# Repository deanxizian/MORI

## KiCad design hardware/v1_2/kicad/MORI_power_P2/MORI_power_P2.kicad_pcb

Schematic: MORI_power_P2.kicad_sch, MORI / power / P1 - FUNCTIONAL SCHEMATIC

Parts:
C1, C20, C40: 100n; C_0603_1608Metric
C2: 1u 25V; C_0603_1608Metric
C10: Panasonic EEU-FR1C102 1000uF 16V; CP_Radial_D10.0mm_P5.00mm__P2_C10
C21, C41: 10n; C_0603_1608Metric
C30: Panasonic EEU-FR1C102 1000uF 16V; CP_Radial_D10.0mm_P5.00mm
D1, D20, D40: BZT52H-C10,115; D_SOD-123F
D10, D30: B540C-13-F; D_SMC
H1, H2, H3, H4: M2 clearance; MountingHole_2.2mm_M2
J1: PACK AFTER 6.3A FUSE / MASTER; AMASS_XT30UPB-M_1x02_P5.0mm_Vertical
J2: WHEEL BUCK VIN; AMASS_XT30UPB-M_1x02_P5.0mm_Vertical
J3: WHEEL BUCK 9V RETURN; AMASS_XT30UPB-M_1x02_P5.0mm_Vertical
J4: HEAD BUCK VIN; AMASS_XT30UPB-M_1x02_P5.0mm_Vertical__P2_J4
J5: HEAD BUCK 6V RETURN; AMASS_XT30UPB-M_1x02_P5.0mm_Vertical__P2_J5
J6: LOGIC BUCKS VIN / FUSED HARNESS; AMASS_XT30UPB-M_1x02_P5.0mm_Vertical
J7: S288 L; JST_XH_B3B-XH-A_1x03_P2.50mm_Vertical__P2_J7
J8: S288 R; JST_XH_B3B-XH-A_1x03_P2.50mm_Vertical__P2_J8
J9: SCS0009 CHAIN; JST_XH_B3B-XH-A_1x03_P2.50mm_Vertical
J10: MOTION CONTROL; JST_GH_BM08B-GHS-TBT_1x08-1MP_P1.25mm_Vertical__P2_J10
J11: WHEEL DUMP 5R6 EXTERNAL; AMASS_XT30UPB-M_1x02_P5.0mm_Vertical
J12: HEAD DUMP 10R EXTERNAL; AMASS_XT30UPB-M_1x02_P5.0mm_Vertical__P2_J12
J13: S288 DATA; JST_GH_BM02B-GHS-TBT_1x02-1MP_P1.25mm_Vertical__P2_J13
J14: HEAD DATA; JST_GH_BM03B-GHS-TBT_1x03-1MP_P1.25mm_Vertical
J15: CHARGE INTERLOCK; JST_GH_BM02B-GHS-TBT_1x02-1MP_P1.25mm_Vertical
J16: CHARGER RAW VBUS SENSE; JST_GH_BM02B-GHS-TBT_1x02-1MP_P1.25mm_Vertical__P2_J16
Q1, Q10, Q30: AO4407A; SOIC-8_3.9x4.9mm_P1.27mm
Q11, Q20, Q31, Q40: AO3400A; SOT-23
Q50: MMBT3904LT1G; SOT-23
R1, R10, R30, R54: 10k; R_0603_1608Metric
R2: WSL2512R0100FEA 10mR 1% 1W; R_2512_6332Metric
R3, R4: 0; R_0603_1608Metric
R11, R31: 100; R_0603_1608Metric
R20, R24, R40, R44: 2.2k; R_0603_1608Metric
R21: 33.2k 0.1%; R_0603_1608Metric
R22, R26, R42, R46: 10k 0.1%; R_0603_1608Metric
R23, R43: 1M 0.1%; R_0603_1608Metric
R25: 37.4k 0.1%; R_0603_1608Metric
R41: 16.5k 0.1%; R_0603_1608Metric
R45: 18.7k 0.1%; R_0603_1608Metric
R50, R52: 100k 0.1%; R_0603_1608Metric
R51, R53: 27k 0.1%; R_0603_1608Metric
R55: 47k; R_0603_1608Metric
R56: 100k; R_0603_1608Metric
U1: INA180A1IDBVR; SOT-23-5
U20, U40: LM393BDR; SOIC-8_3.9x4.9mm_P1.27mm
U21, U41: TL431BIDBZR; SOT-23

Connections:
/+3V3: C1.1, J10.1, U1.5 (VS)
/ARM_Q: J10.2, Q11.1, Q31.1, R54.1
/BAT_ADC: J10.5, R50.2, R51.1
/BAT_IN: J1.2 (PLUS), Q1.5, Q1.6, Q1.7, Q1.8
/BAT_MON: C2.1, J2.2 (PLUS), J4.2 (PLUS), J6.2 (PLUS), R2.2, R4.1, R50.1
/BAT_REV: D1.1, Q1.1 (SOURCE PROTECTED OUTPUT), Q1.2, Q1.3, R2.1, R3.1
/CHG_BASE: Q50.1 (B), R55.2, R56.1
/CHG_N: J10.4, J15.1, Q50.3 (C)
/CURRENT_ADC: J10.7, U1.1 (OUT)
/FAULT_N: J10.3, U20.7 (OUT2), U40.7 (OUT2)
/GND: C1.2, C2.2, C10.2, C20.2, C21.2, C30.2, C40.2, C41.2, D20.2, D40.2, J1.1 (MINUS), J2.1 (MINUS), J3.1 (MINUS), J4.1 (MINUS), J5.1 (MINUS), J6.1 (MINUS), J7.1 (GND), J8.1 (GND), J9.1 (GND), J10.8, J13.2, J14.2, J15.2, J16.2, Q11.2, Q20.2, Q31.2, Q40.2, Q50.2 (E), R1.2, R22.2, R26.2, R42.2, R46.2, R51.2, R53.2, R54.2, R56.2, U1.2 (GND), U20.4 (GND), U21.3 (A), U40.4 (GND), U41.3 (A)
/H6_IN: D30.2, J5.2 (PLUS)
/H_BRAKE_GATE: D40.1, Q40.1, R43.1, R44.2, U40.1 (OUT1)
/H_BUS: J9.3 (BUS), J14.1
/H_DUMP_D: J12.1 (MINUS), Q40.3
/H_GATE: Q30.4, R30.1, R31.1
/H_GATE_LOW: Q31.3, R31.2
/H_OVSENSE: C41.1, R45.2, R46.1, U40.6 (IN2-)
/H_PRE: D30.1, Q30.1, Q30.2, Q30.3, R30.2
/H_REF: R40.2, U40.2 (IN1-), U40.5 (IN2+), U41.1 (K), U41.2 (REF)
/H_SENSE: R41.2, R42.1, R43.2, U40.3 (IN1+)
/H_VM: C30.1, C40.1, J9.2 (V+), J12.2 (PLUS), Q30.5 (DRAIN SWITCHED OUTPUT), Q30.6, Q30.7, Q30.8, R40.1, R41.1, R44.1, R45.1, U40.8 (VCC)
/KELVIN_N: R4.2, U1.4 (IN-)
/KELVIN_P: R3.2, U1.3 (IN+)
/REV_GATE: D1.2, Q1.4, R1.1
/VBUS_CHARGE: J16.1, R55.1
/W9_IN: D10.2, J3.2 (PLUS)
/WHEEL_ADC: J10.6, R52.2, R53.1
/W_BRAKE_GATE: D20.1, Q20.1, R23.1, R24.2, U20.1 (OUT1)
/W_BUS: J7.3 (BUS), J8.3 (BUS), J13.1
/W_DUMP_D: J11.1 (MINUS), Q20.3
/W_GATE: Q10.4, R10.1, R11.1
/W_GATE_LOW: Q11.3, R11.2
/W_OVSENSE: C21.1, R25.2, R26.1, U20.6 (IN2-)
/W_PRE: D10.1, Q10.1, Q10.2, Q10.3, R10.2
/W_REF: R20.2, U20.2 (IN1-), U20.5 (IN2+), U21.1 (K), U21.2 (REF)
/W_SENSE: R21.2, R22.1, R23.2, U20.3 (IN1+)
/W_VM: C10.1, C20.1, J7.2 (V+), J8.2 (V+), J11.2 (PLUS), Q10.5 (DRAIN SWITCHED OUTPUT), Q10.6, Q10.7, Q10.8, R20.1, R21.1, R24.1, R25.1, R52.1, U20.8 (VCC)

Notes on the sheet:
MORI / POWER CONDITIONER / S2
Power flows left to right. Supplies above, returns below. PROTOTYPE / UNVALIDATED.
01 Pack input / reverse protection / shunt
External pack, fuse and master switch precede J1. No charger on this PCB.
10mR / 1% / 1W
02 Kelvin current sense
Sense from the shunt pads. Discharge-only nominal transfer: 0.2 V/A.
03 Wheel 9 V conditioning
External buck return. Inrush, brake energy and thermal performance: NOT_TESTED.
1000u / 16V
04 Head 6 V conditioning
05 External converter input distribution
J2 -> wheel buck; J4 -> head buck; J6 -> two independent 5 V converters.
06 Wheel rail / brake and overvoltage
Two comparators share one LM393B. External dump resistor needs pulse qualification.
LM393B / brake + fault
5R6 / 5W external
07 Head rail / brake and overvoltage
10R / 5W external
08 Voltage monitor / motion connector
Divider ratio 27 / 127. Current_ADC comes from block 02.
09 Charge insertion / VBUS sense
Sense and interlock only; no CC / PD / CC-CV charger implementation.
10 Supply boundaries / board mounting
80 x 45 mm PCB; populated assembly and thermal performance are not qualified.
Supply boundary

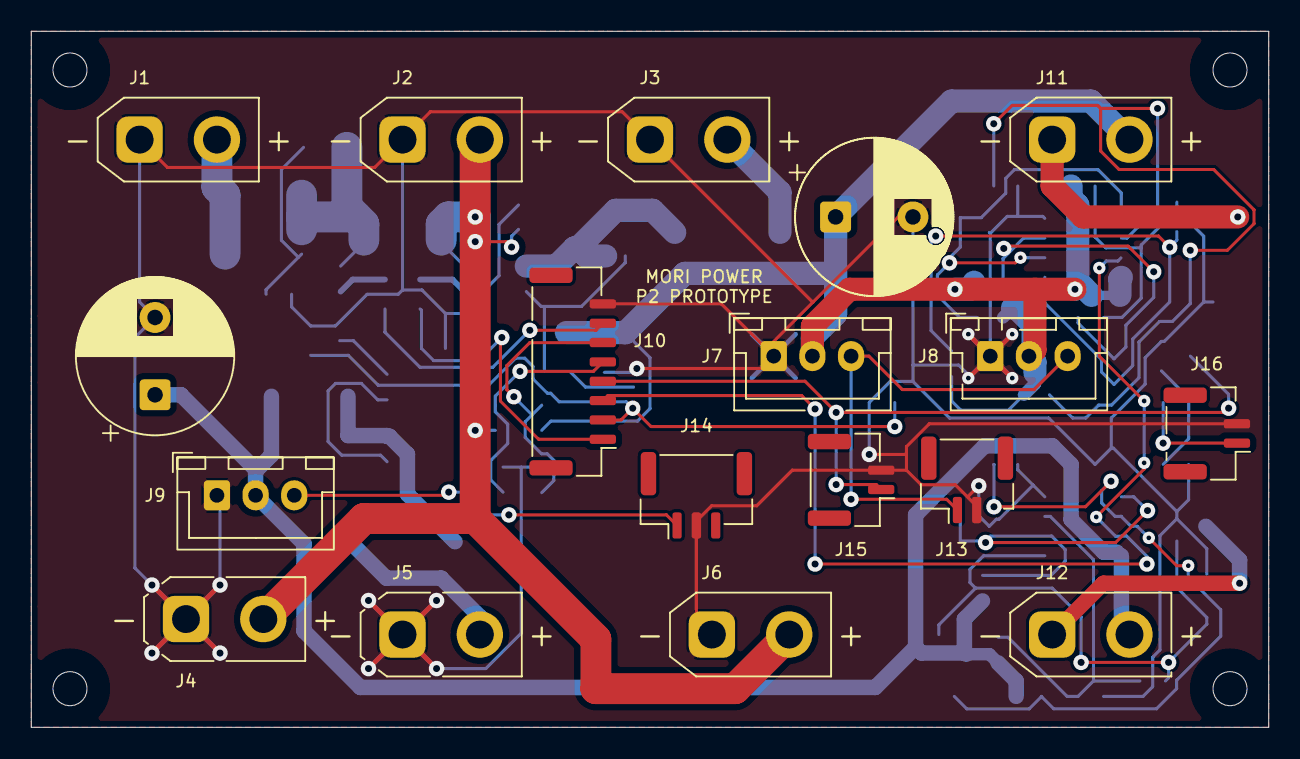
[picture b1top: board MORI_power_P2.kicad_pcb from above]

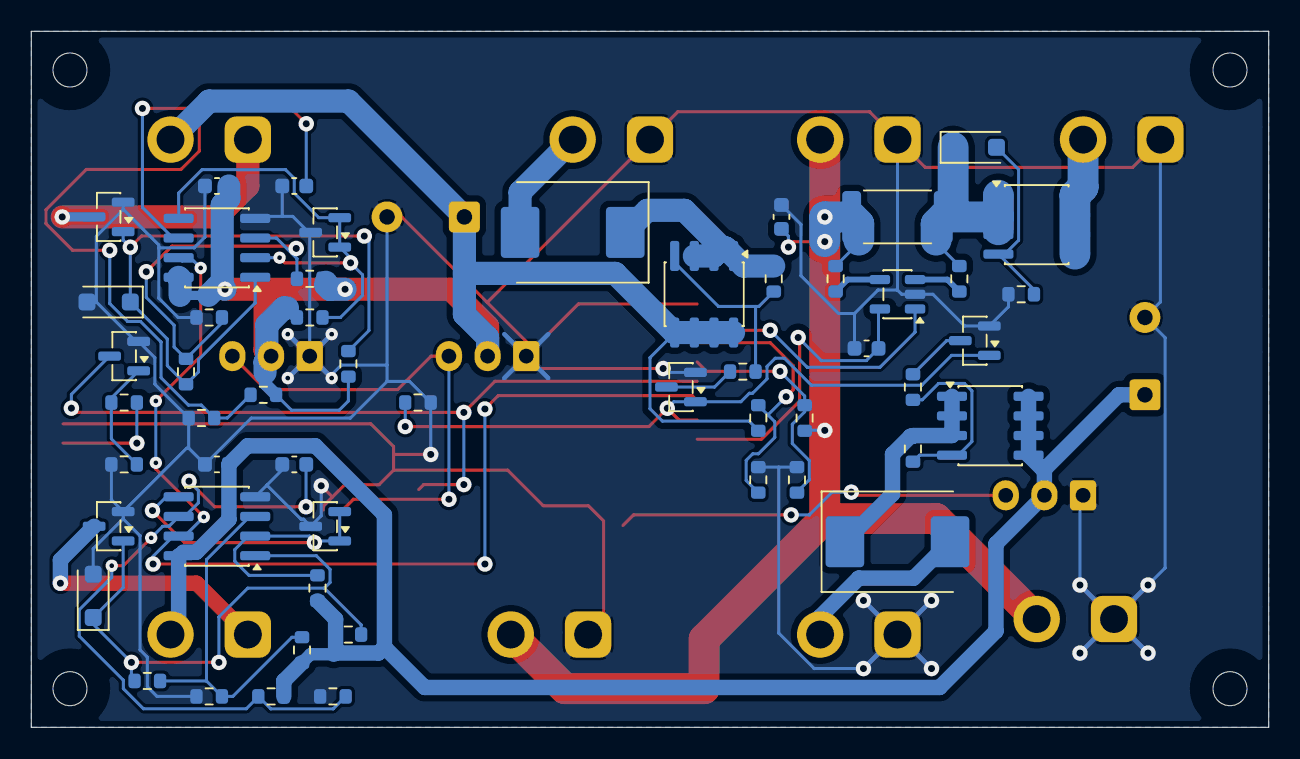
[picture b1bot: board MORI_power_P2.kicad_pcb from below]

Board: 2 copper layers, 80.0 x 45.0 mm, 75 parts (53 on the bottom side), 38 nets.

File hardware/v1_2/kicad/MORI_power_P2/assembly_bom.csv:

ref,value,footprint,source,note
J1,PACK AFTER 6.3A FUSE / MASTER,Connector_AMASS:AMASS_XT30UPB-M_1x02_P5.0mm_Vertical,,"AMASS XT30UPB-M PCB: pin1 minus, pin2 plus; mating housing polarization plus continuity check mandatory."
J2,WHEEL BUCK VIN,Connector_AMASS:AMASS_XT30UPB-M_1x02_P5.0mm_Vertical,,"AMASS XT30UPB-M PCB: pin1 minus, pin2 plus; mating housing polarization plus continuity check mandatory."
J3,WHEEL BUCK 9V RETURN,Connector_AMASS:AMASS_XT30UPB-M_1x02_P5.0mm_Vertical,,"AMASS XT30UPB-M PCB: pin1 minus, pin2 plus; mating housing polarization plus continuity check mandatory."
J4,HEAD BUCK VIN,MORI_Custom:AMASS_XT30UPB-M_1x02_P5.0mm_Vertical__P2_J4,,"AMASS XT30UPB-M PCB: pin1 minus, pin2 plus; mating housing polarization plus continuity check mandatory."
J5,HEAD BUCK 6V RETURN,MORI_Custom:AMASS_XT30UPB-M_1x02_P5.0mm_Vertical__P2_J5,,"AMASS XT30UPB-M PCB: pin1 minus, pin2 plus; mating housing polarization plus continuity check mandatory."
J6,LOGIC BUCKS VIN / FUSED HARNESS,Connector_AMASS:AMASS_XT30UPB-M_1x02_P5.0mm_Vertical,,"AMASS XT30UPB-M PCB: pin1 minus, pin2 plus; mating housing polarization plus continuity check mandatory."
J11,WHEEL DUMP 5R6 EXTERNAL,Connector_AMASS:AMASS_XT30UPB-M_1x02_P5.0mm_Vertical,,"AMASS XT30UPB-M PCB: pin1 minus, pin2 plus; mating housing polarization plus continuity check mandatory."
J12,HEAD DUMP 10R EXTERNAL,MORI_Custom:AMASS_XT30UPB-M_1x02_P5.0mm_Vertical__P2_J12,,"AMASS XT30UPB-M PCB: pin1 minus, pin2 plus; mating housing polarization plus continuity check mandatory."
J7,S288 L,MORI_Custom:JST_XH_B3B-XH-A_1x03_P2.50mm_Vertical__P2_J7,,Board-side XH 3-pin interface only. SCS original 5264-3P uses 1GND/2VCC/3TTL. S288 factory mating plug remains unverified; adapter harness must be confirmed.
J8,S288 R,MORI_Custom:JST_XH_B3B-XH-A_1x03_P2.50mm_Vertical__P2_J8,,Board-side XH 3-pin interface only. SCS original 5264-3P uses 1GND/2VCC/3TTL. S288 factory mating plug remains unverified; adapter harness must be confirmed.
J9,SCS0009 CHAIN,Connector_JST:JST_XH_B3B-XH-A_1x03_P2.50mm_Vertical,,Board-side XH 3-pin interface only. SCS original 5264-3P uses 1GND/2VCC/3TTL. S288 factory mating plug remains unverified; adapter harness must be confirmed.
J10,MOTION CONTROL,MORI_Custom:JST_GH_BM08B-GHS-TBT_1x08-1MP_P1.25mm_Vertical__P2_J10,,Pin numbers are PCB connector numbers; harness mating view must be continuity checked.
J13,S288 DATA,MORI_Custom:JST_GH_BM02B-GHS-TBT_1x02-1MP_P1.25mm_Vertical__P2_J13,,Pin numbers are PCB connector numbers; harness mating view must be continuity checked.
J14,HEAD DATA,Connector_JST:JST_GH_BM03B-GHS-TBT_1x03-1MP_P1.25mm_Vertical,,Pin numbers are PCB connector numbers; harness mating view must be continuity checked.
J15,CHARGE INTERLOCK,Connector_JST:JST_GH_BM02B-GHS-TBT_1x02-1MP_P1.25mm_Vertical,,Pin numbers are PCB connector numbers; harness mating view must be continuity checked.
J16,CHARGER RAW VBUS SENSE,MORI_Custom:JST_GH_BM02B-GHS-TBT_1x02-1MP_P1.25mm_Vertical__P2_J16,,Pin numbers are PCB connector numbers; harness mating view must be continuity checked.
Q1,AO4407A,Package_SO:SOIC-8_3.9x4.9mm_P1.27mm,https://www.aosmd.com/sites/default/files/res/datasheets/AO4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,
R1,10k,Resistor_SMD:R_0603_1608Metric,,
D1,"BZT52H-C10,115",Diode_SMD:D_SOD-123F,,
R2,WSL2512R0100FEA 10mR 1% 1W,Resistor_SMD:R_2512_6332Metric,,
U1,INA180A1IDBVR,Package_TO_SOT_SMD:SOT-23-5,https://www.ti.com/lit/ds/symlink/ina180.pdf,Kelvin sense of 10mR; gain20 =>0.2V/A. Discharge only; reverse current not measured.
R3,0,Resistor_SMD:R_0603_1608Metric,,
R4,0,Resistor_SMD:R_0603_1608Metric,,
D10,B540C-13-F,Diode_SMD:D_SMC,,Cathode pin1. Prevents regenerative reverse current into buck; forward drop reduces available motor voltage. Exact vendor suffix to qualify.
Q10,AO4407A,Package_SO:SOIC-8_3.9x4.9mm_P1.27mm,https://www.aosmd.com/sites/default/files/res/datasheets/AO4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,
Q11,AO3400A,Package_TO_SOT_SMD:SOT-23,https://www.aosmd.com/sites/default/files/res/datasheets/AO3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,
R10,10k,Resistor_SMD:R_0603_1608Metric,,
R11,100,Resistor_SMD:R_0603_1608Metric,,
C10,Panasonic EEU-FR1C102 1000uF 16V,MORI_Custom:CP_Radial_D10.0mm_P5.00mm__P2_C10,,"D10 x H16; height is vendor capacitor envelope, NOT fitted into old10mm allocation."
D30,B540C-13-F,Diode_SMD:D_SMC,,Cathode pin1. Prevents regenerative reverse current into buck; forward drop reduces available motor voltage. Exact vendor suffix to qualify.
Q30,AO4407A,Package_SO:SOIC-8_3.9x4.9mm_P1.27mm,https://www.aosmd.com/sites/default/files/res/datasheets/AO4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,
Q31,AO3400A,Package_TO_SOT_SMD:SOT-23,https://www.aosmd.com/sites/default/files/res/datasheets/AO3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,
R30,10k,Resistor_SMD:R_0603_1608Metric,,
R31,100,Resistor_SMD:R_0603_1608Metric,,
C30,Panasonic EEU-FR1C102 1000uF 16V,Capacitor_THT:CP_Radial_D10.0mm_P5.00mm,,"D10 x H16; height is vendor capacitor envelope, NOT fitted into old10mm allocation."
U20,LM393BDR,Package_SO:SOIC-8_3.9x4.9mm_P1.27mm,https://www.ti.com/lit/ds/symlink/lm393b.pdf,
U21,TL431BIDBZR,Package_TO_SOT_SMD:SOT-23,https://www.ti.com/lit/ds/symlink/tl431.pdf,"DBZ pin1 cathode,2 reference,3 anode. B grade +/-0.5% at25C; thermal error in tolerance model."
Q20,AO3400A,Package_TO_SOT_SMD:SOT-23,https://www.aosmd.com/sites/default/files/res/datasheets/AO3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,
D20,"BZT52H-C10,115",Diode_SMD:D_SOD-123F,,
R20,2.2k,Resistor_SMD:R_0603_1608Metric,,
R21,33.2k 0.1%,Resistor_SMD:R_0603_1608Metric,,
R22,10k 0.1%,Resistor_SMD:R_0603_1608Metric,,
R23,1M 0.1%,Resistor_SMD:R_0603_1608Metric,,
R24,2.2k,Resistor_SMD:R_0603_1608Metric,,
R25,37.4k 0.1%,Resistor_SMD:R_0603_1608Metric,,
R26,10k 0.1%,Resistor_SMD:R_0603_1608Metric,,
C20,100n,Capacitor_SMD:C_0603_1608Metric,,
C21,10n,Capacitor_SMD:C_0603_1608Metric,,
U40,LM393BDR,Package_SO:SOIC-8_3.9x4.9mm_P1.27mm,https://www.ti.com/lit/ds/symlink/lm393b.pdf,
U41,TL431BIDBZR,Package_TO_SOT_SMD:SOT-23,https://www.ti.com/lit/ds/symlink/tl431.pdf,"DBZ pin1 cathode,2 reference,3 anode. B grade +/-0.5% at25C; thermal error in tolerance model."
Q40,AO3400A,Package_TO_SOT_SMD:SOT-23,https://www.aosmd.com/sites/default/files/res/datasheets/AO3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,
D40,"BZT52H-C10,115",Diode_SMD:D_SOD-123F,,
R40,2.2k,Resistor_SMD:R_0603_1608Metric,,
R41,16.5k 0.1%,Resistor_SMD:R_0603_1608Metric,,
R42,10k 0.1%,Resistor_SMD:R_0603_1608Metric,,
R43,1M 0.1%,Resistor_SMD:R_0603_1608Metric,,
R44,2.2k,Resistor_SMD:R_0603_1608Metric,,
R45,18.7k 0.1%,Resistor_SMD:R_0603_1608Metric,,
R46,10k 0.1%,Resistor_SMD:R_0603_1608Metric,,
C40,100n,Capacitor_SMD:C_0603_1608Metric,,
C41,10n,Capacitor_SMD:C_0603_1608Metric,,
R50,100k 0.1%,Resistor_SMD:R_0603_1608Metric,,
R51,27k 0.1%,Resistor_SMD:R_0603_1608Metric,,
R52,100k 0.1%,Resistor_SMD:R_0603_1608Metric,,
R53,27k 0.1%,Resistor_SMD:R_0603_1608Metric,,
R54,10k,Resistor_SMD:R_0603_1608Metric,,
R55,47k,Resistor_SMD:R_0603_1608Metric,,
R56,100k,Resistor_SMD:R_0603_1608Metric,,
C1,100n,Capacitor_SMD:C_0603_1608Metric,,
C2,1u 25V,Capacitor_SMD:C_0603_1608Metric,,
Q50,MMBT3904LT1G,Package_TO_SOT_SMD:SOT-23,,SOT23 1B 2E 3C. Raw VBUS detect only; neither CC nor charging control.
H1,M2 clearance,MountingHole:MountingHole_2.2mm_M2,,
H2,M2 clearance,MountingHole:MountingHole_2.2mm_M2,,
H3,M2 clearance,MountingHole:MountingHole_2.2mm_M2,,
H4,M2 clearance,MountingHole:MountingHole_2.2mm_M2,,

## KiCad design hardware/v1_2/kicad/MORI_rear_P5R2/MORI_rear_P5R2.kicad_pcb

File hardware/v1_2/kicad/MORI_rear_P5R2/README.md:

# MORI_rear_P5R2

PROTOTYPE / 实物 NOT_TESTED。P5R2逐网复查版；电路、器件型号和针脚不变。

当前ERC/DRC/未连接/一致性均0，完整报告与局部例外见 ../../layout_P5R2/README.md。本目录没有制造释放。

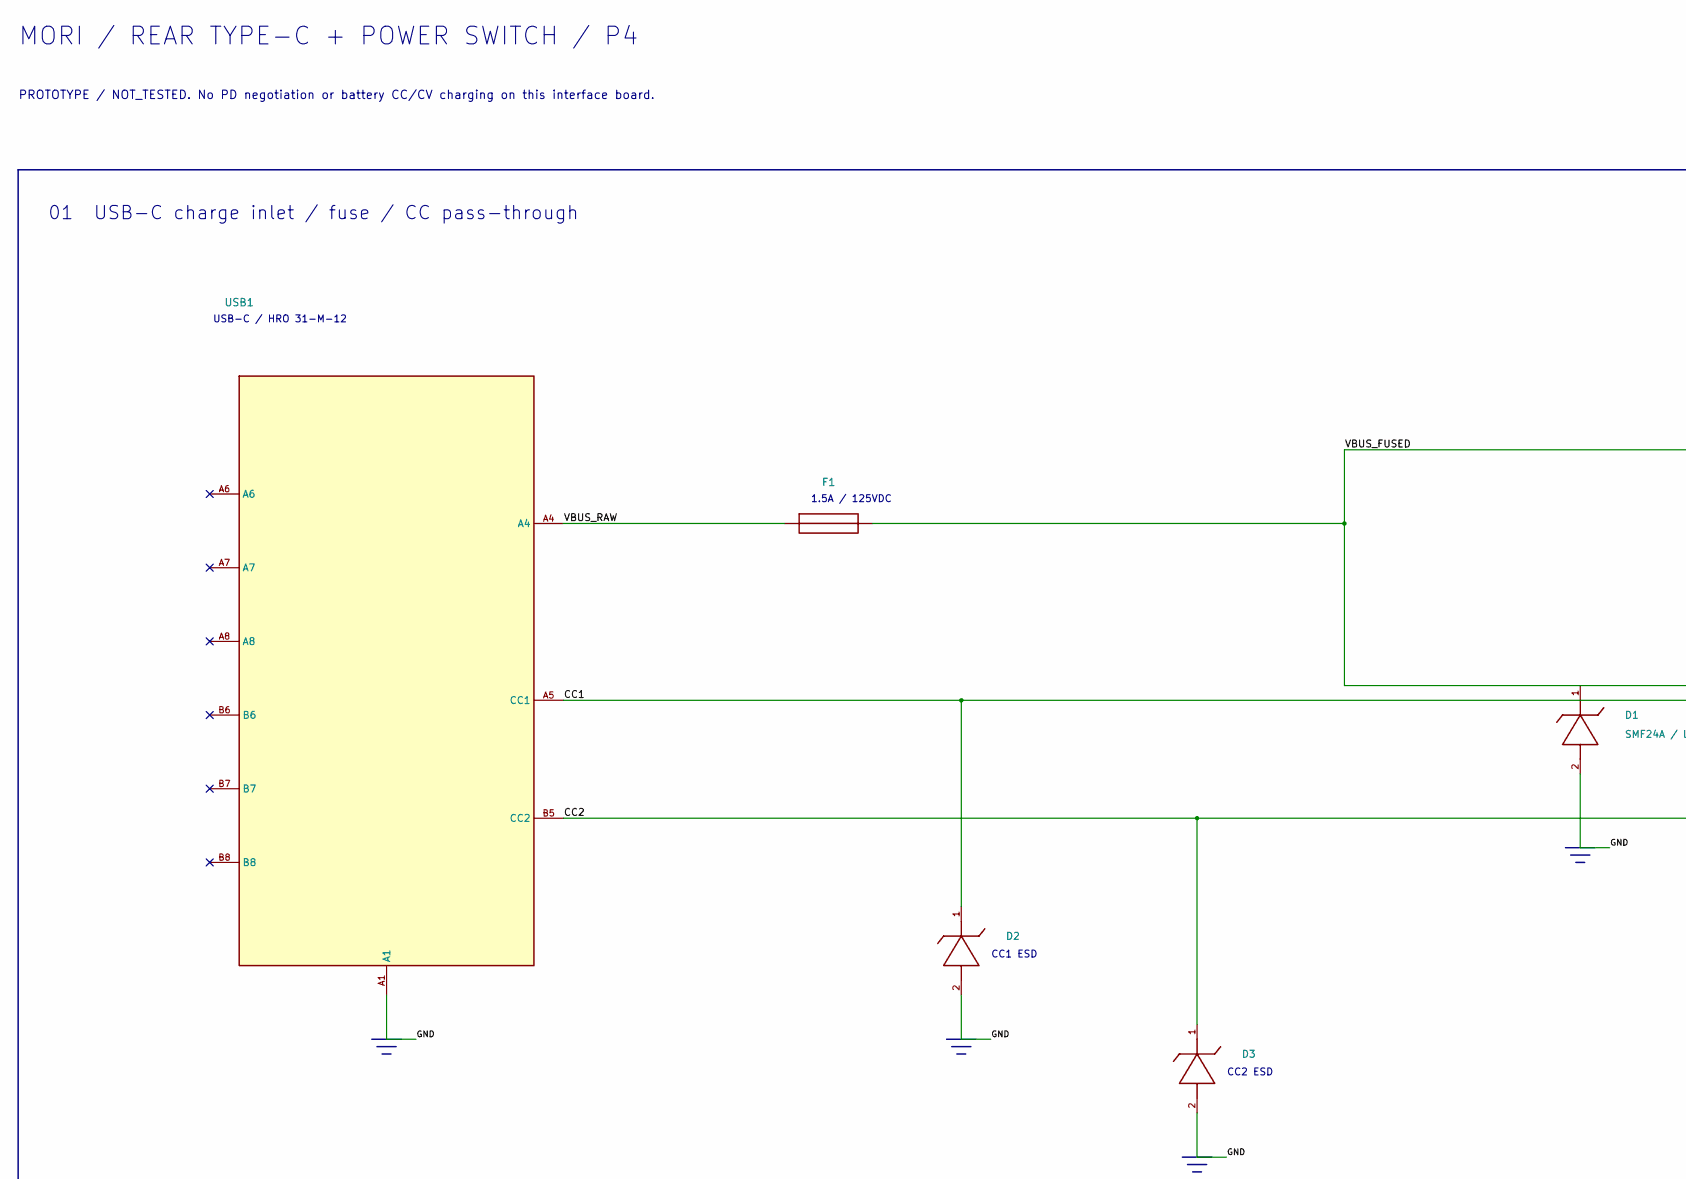
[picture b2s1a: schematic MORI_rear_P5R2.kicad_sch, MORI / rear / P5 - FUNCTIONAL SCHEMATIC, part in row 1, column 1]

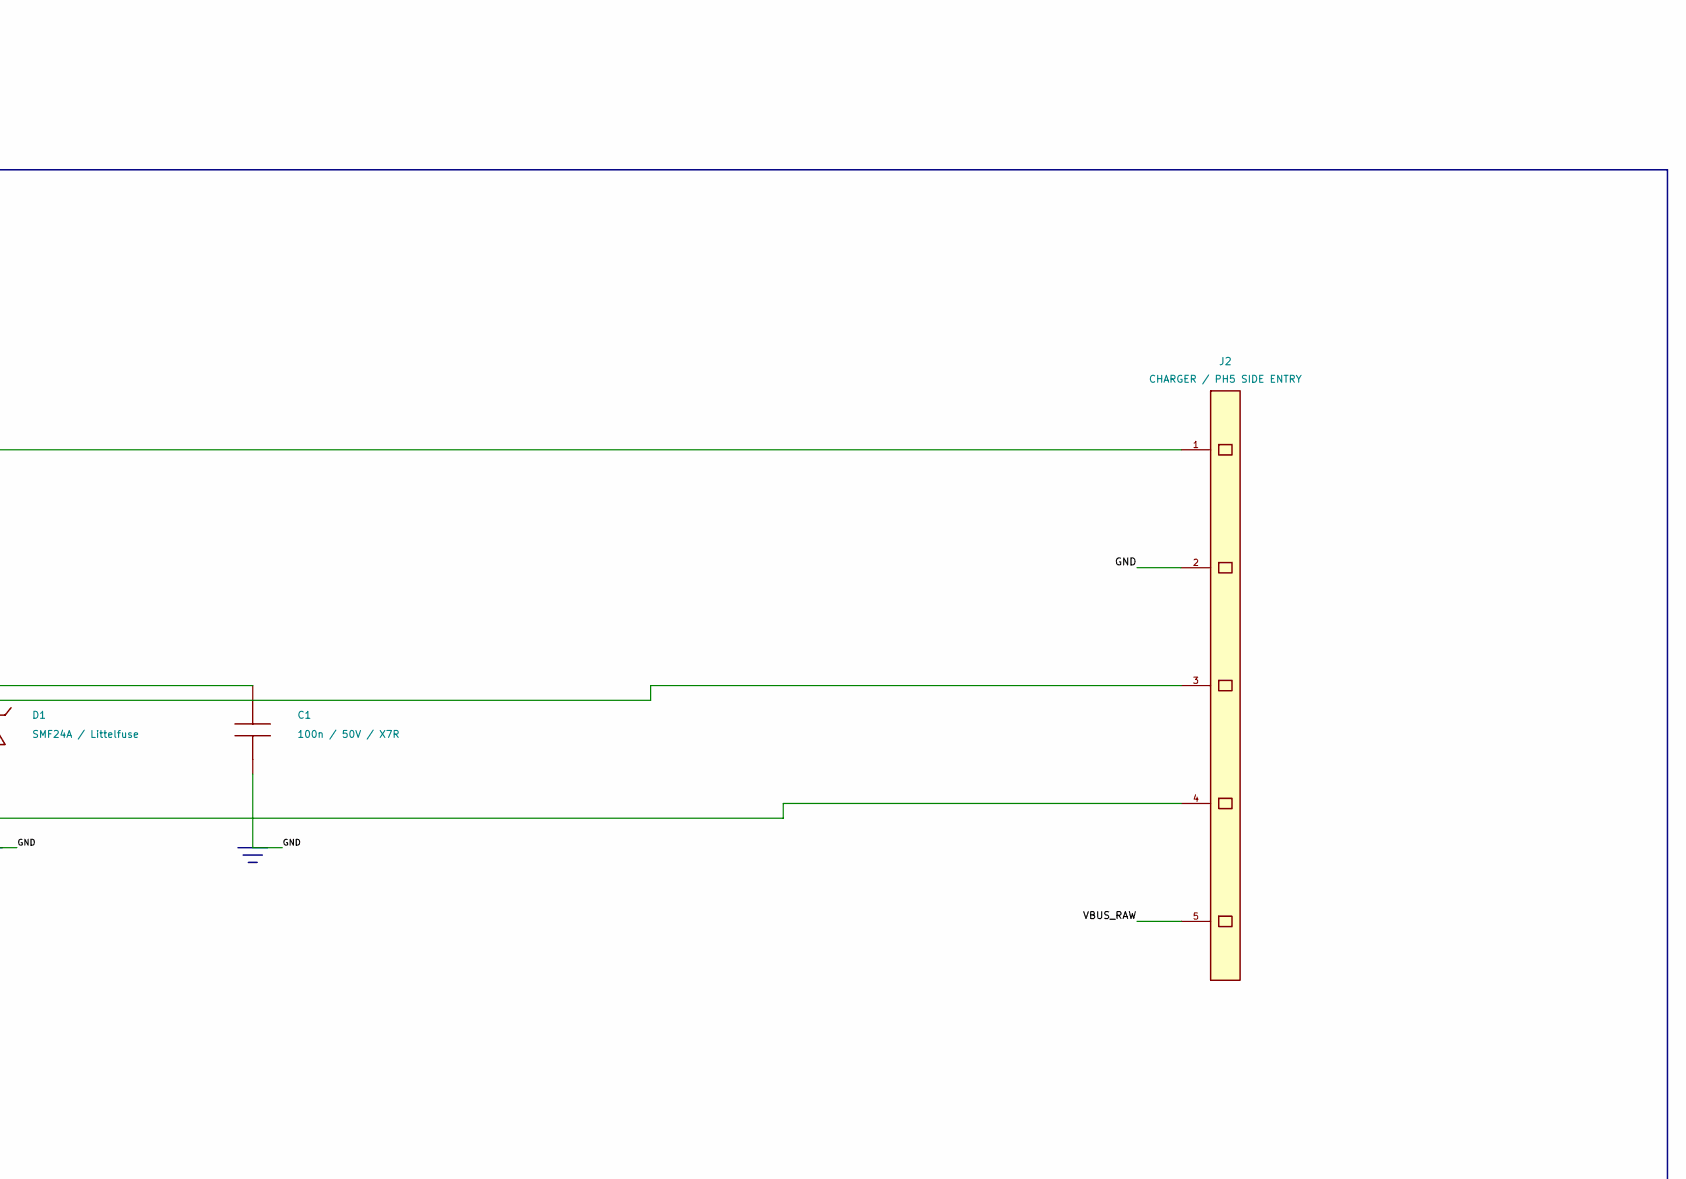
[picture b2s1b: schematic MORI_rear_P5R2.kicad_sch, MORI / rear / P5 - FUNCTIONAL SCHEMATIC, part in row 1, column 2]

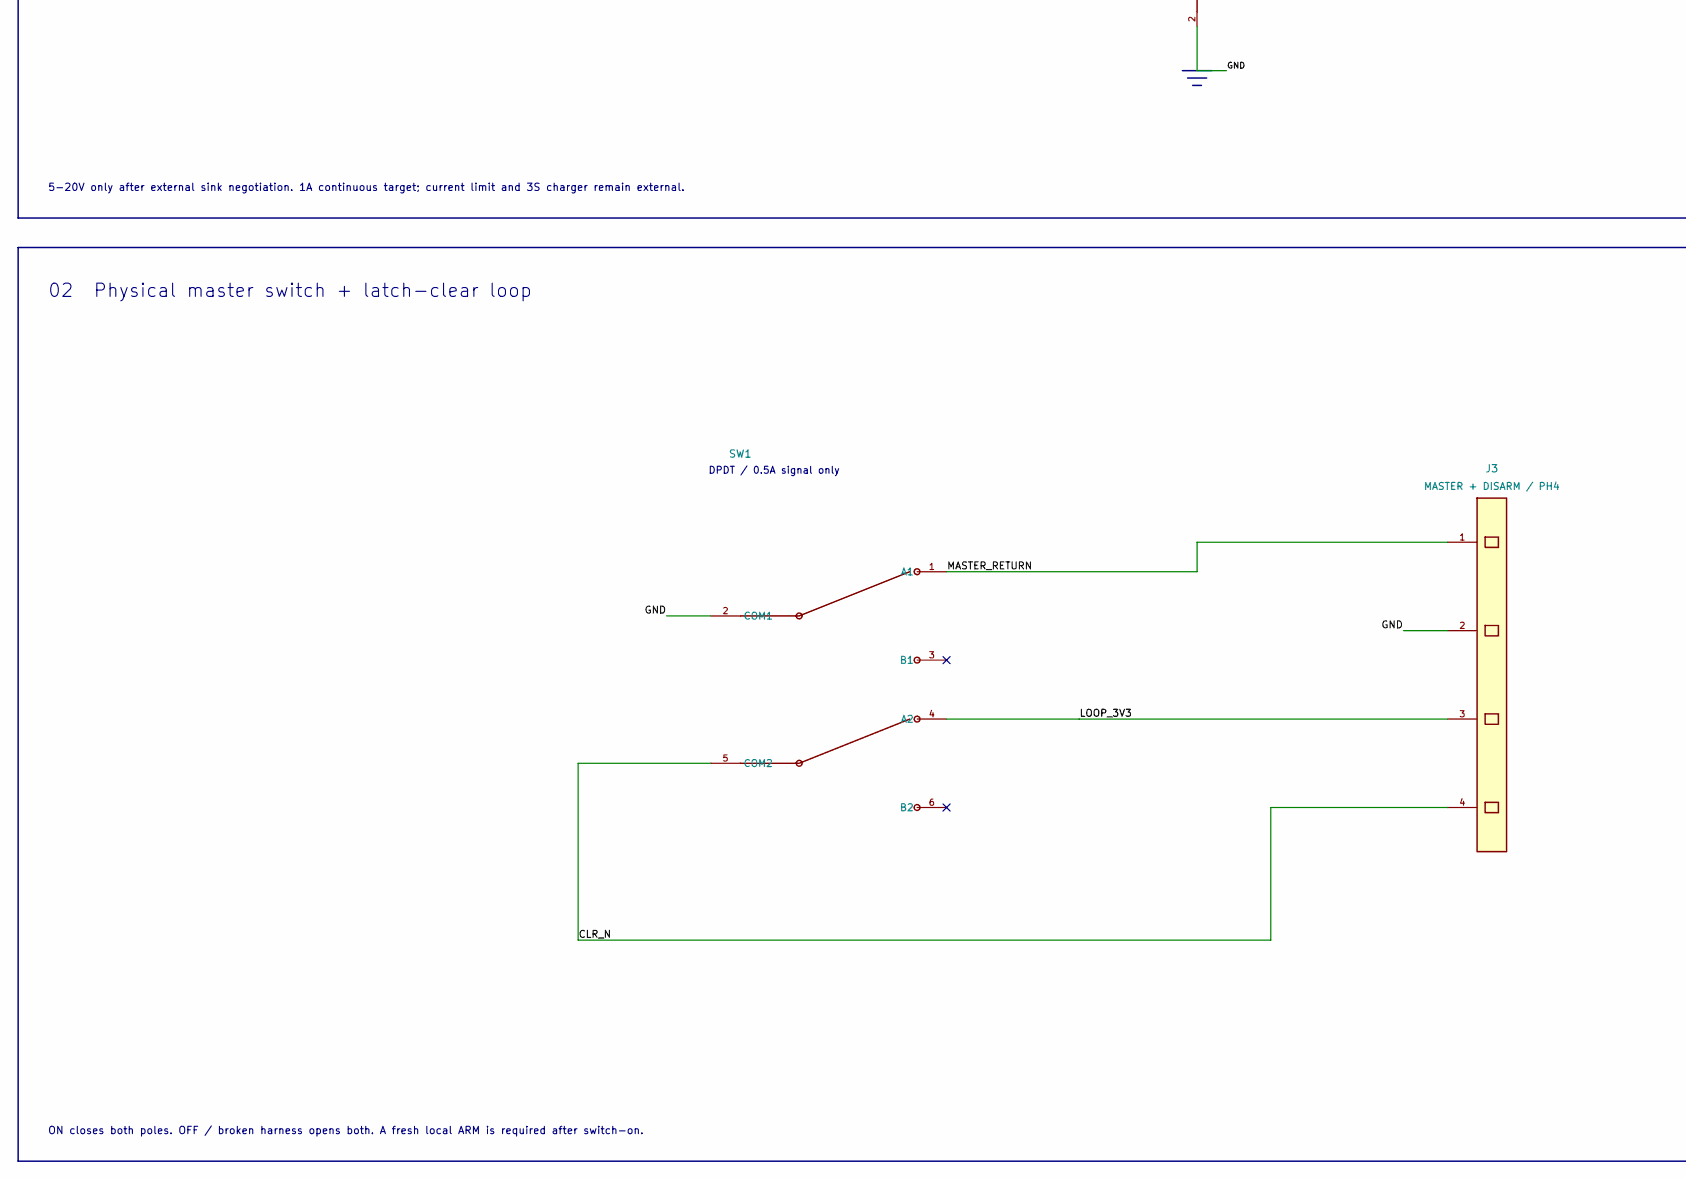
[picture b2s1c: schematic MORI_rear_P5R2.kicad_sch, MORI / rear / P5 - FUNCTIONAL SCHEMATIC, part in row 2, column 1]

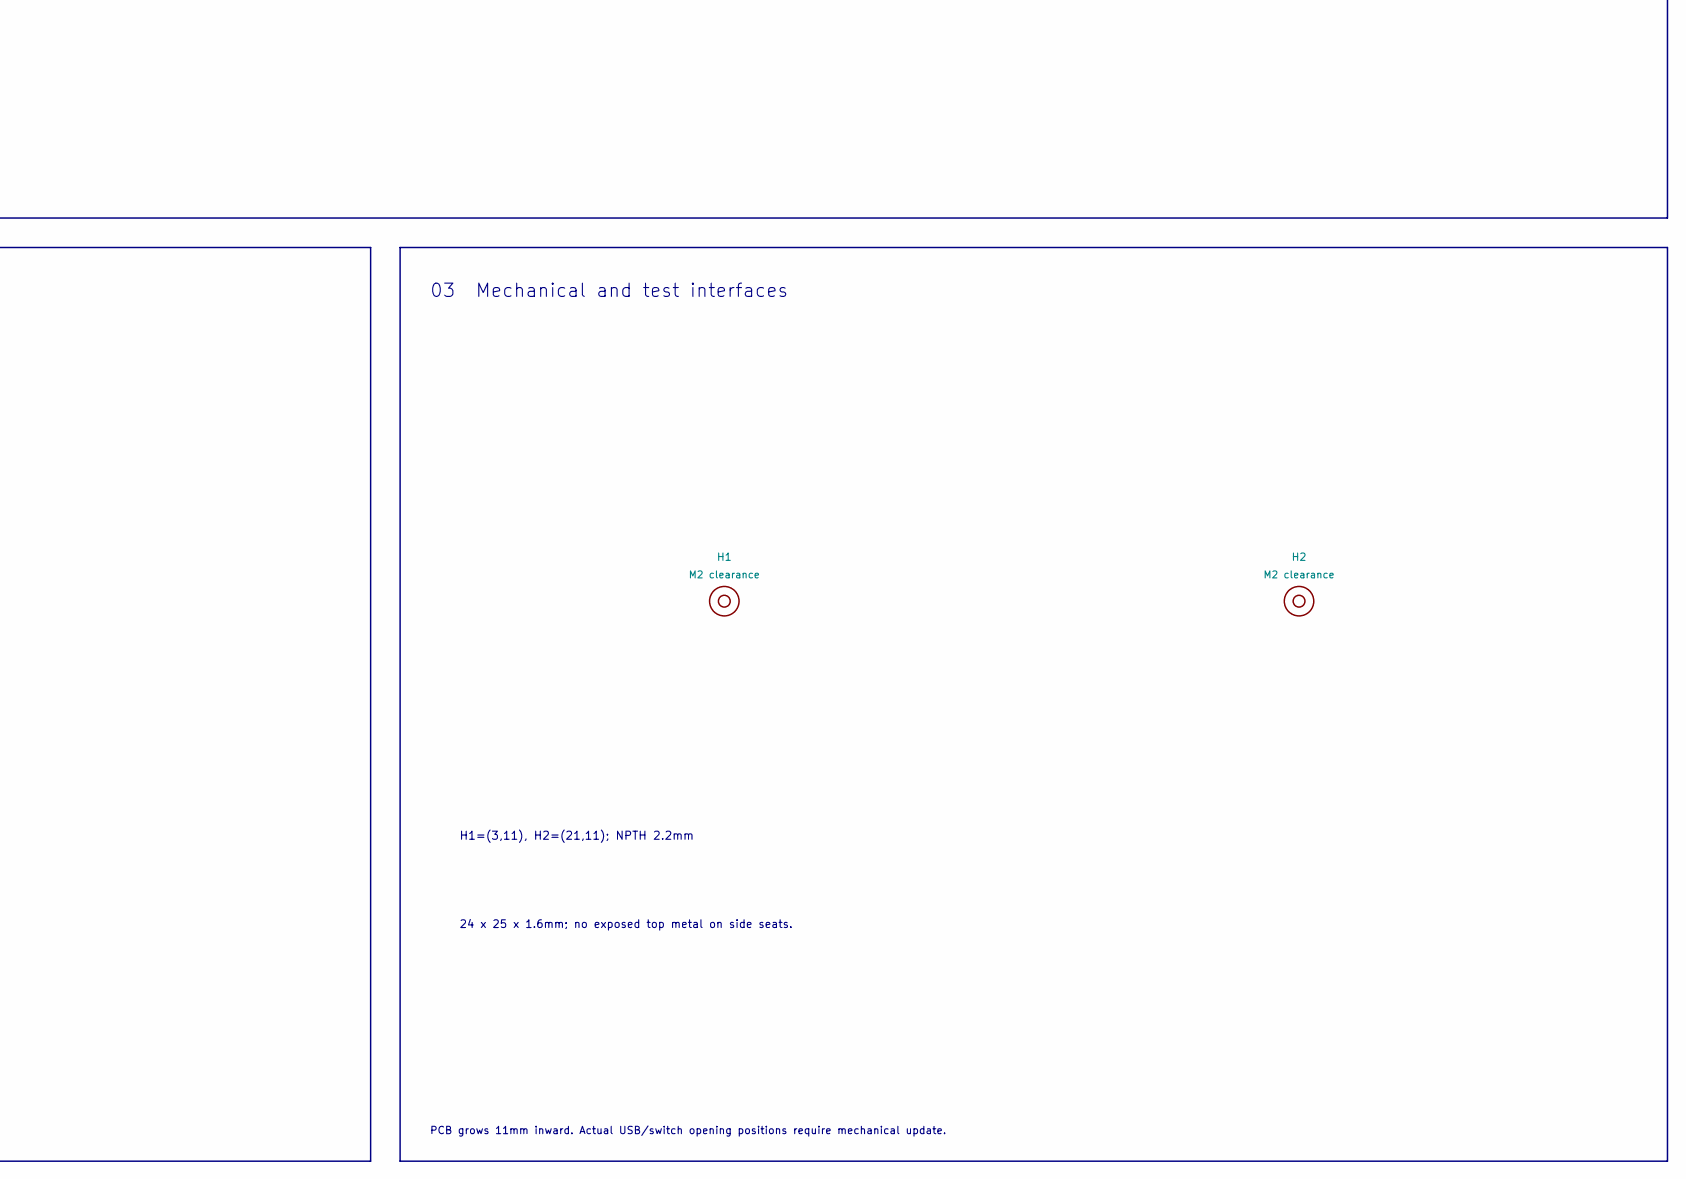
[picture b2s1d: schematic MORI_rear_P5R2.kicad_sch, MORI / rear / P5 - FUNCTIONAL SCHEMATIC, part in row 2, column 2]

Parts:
C1: 100n / 50V / X7R; C_0603_1608Metric
D1: SMF24A / Littelfuse; D_SOD-123F
D2: PESD5V0L1BA,115; D_SOD-323__P5_D2
D3: PESD5V0L1BA,115; D_SOD-323__P5_D3
F1: 045101.5MRL / 1.5A; Littelfuse_451_6.1x2.69_P4__P3R1_F1
H1, H2: M2 clearance; MountingHole_2.2mm_M2
J2: CHARGER / PH5 SIDE ENTRY; JST_PH_S5B-PH-K_1x05_P2.00mm_Horizontal__P4_ANNULUS__P5_J2
J3: MASTER + DISARM / PH4; JST_PH_B4B-PH-K_1x04_P2.00mm_Vertical__P4_ANNULUS__P3R1_J3
SW1: SOFNG MS-202V-G3; SOFNG_MS202V_G3_P4__P3R1_SW1
USB1: HRO TYPE-C-31-M-12 / charge only; USB_C_Receptacle_HRO_TYPE-C-31-M-12__P4_ANNULUS__P5_USB1

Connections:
/CC1: D2.1, J2.3, USB1.A5 (CC1)
/CC2: D3.1, J2.4, USB1.B5 (CC2)
/CLR_N: J3.4, SW1.5 (COM2)
/GND: C1.2, D1.2, D2.2, D3.2, J2.2, J3.2, SW1.2 (COM1), USB1.A1, USB1.A12, USB1.B1, USB1.B12, USB1.SH
/LOOP_3V3: J3.3, SW1.4 (A2)
/MASTER_RETURN: J3.1, SW1.1 (A1)
/VBUS_FUSED: C1.1, D1.1, F1.2, J2.1
/VBUS_RAW: F1.1, J2.5, USB1.A4, USB1.A9, USB1.B4, USB1.B9

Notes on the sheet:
MORI / REAR TYPE-C + POWER SWITCH / P4
PROTOTYPE / NOT_TESTED. No PD negotiation or battery CC/CV charging on this interface board.
01 USB-C charge inlet / fuse / CC pass-through
5-20V only after external sink negotiation. 1A continuous target; current limit and 3S charger remain external.
USB-C / HRO 31-M-12
1.5A / 125VDC
CC1 ESD
CC2 ESD
02 Physical master switch + latch-clear loop
ON closes both poles. OFF / broken harness opens both. A fresh local ARM is required after switch-on.
DPDT / 0.5A signal only
03 Mechanical and test interfaces
PCB grows 11mm inward. Actual USB/switch opening positions require mechanical update.
H1=(3,11), H2=(21,11); NPTH 2.2mm
24 x 25 x 1.6mm; no exposed top metal on side seats.

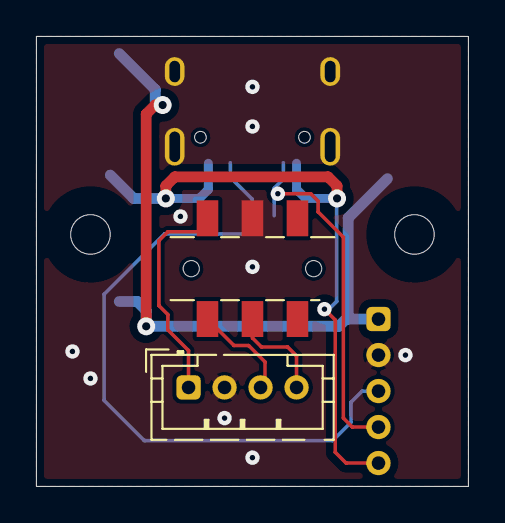
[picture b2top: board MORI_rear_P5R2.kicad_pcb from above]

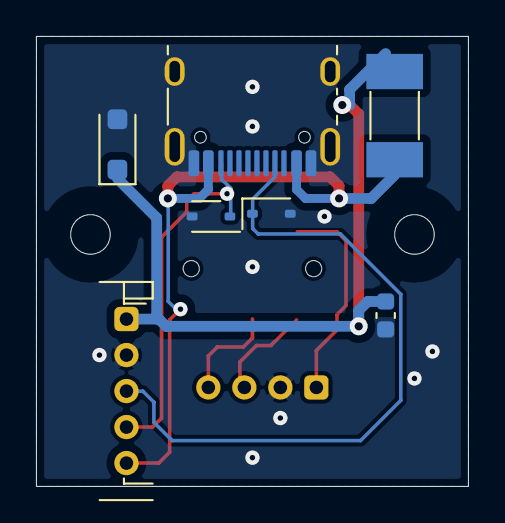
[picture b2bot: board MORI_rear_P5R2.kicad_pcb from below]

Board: 2 copper layers, 24.0 x 25.0 mm, 11 parts (7 on the bottom side), 8 nets.
